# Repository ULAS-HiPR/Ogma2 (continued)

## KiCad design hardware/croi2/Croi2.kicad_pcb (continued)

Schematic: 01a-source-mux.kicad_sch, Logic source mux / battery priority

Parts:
C1101: 10n 16V X7R; C_0603_1608Metric
C1102: 100n 16V X7R; C_0603_1608Metric
C1103: 100n 16V X7R; C_0402_1005Metric; MPN CL05B104KB54PNC; LCSC C307331
C1104, C1105: 1u 16V X7R; C_0603_1608Metric
C1106: 2.2u 16V X7R; C_0603_1608Metric
R1101: 40.2k 0.1%; R_0603_1608Metric
R1102, R1104, R1106: 10k 0.1%; R_0603_1608Metric
R1103: 75k 0.1%; R_0603_1608Metric
R1105: 43.2k 0.1%; R_0603_1608Metric
R1107: 44.2k 1%; R_0603_1608Metric
R1108: 100k; R_0402_1005Metric; MPN 0402WGF1003TCE; LCSC C25741
U1101: TPS2121RUXR; MPN TPS2121RUXR
U1102: TPS70933DBVR; MPN TPS70933DBVR

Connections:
BOOT_3V3: C1106.1, R1108.1, U1102.5 (OUT); also elsewhere on the board
GND: C1101.2, C1102.2, C1103.2, C1104.2, C1105.2, C1106.2, R1102.2, R1104.2, R1106.2, R1107.2, U1101.3 (GND_[3,12]), U1101.12, U1102.2 (GND); also elsewhere on the board
LOGIC_SELECTED: C1104.1, C1105.1, U1101.1 (SUPPLY_[1,8]), U1101.8, U1102.1 (SUPPLY_[1,3]), U1102.3; also elsewhere on the board
MUX_ILIM: R1107.1, U1101.10 (ILIM)
MUX_OV_BAT: R1103.2, R1104.1, U1101.5 (OV1)
MUX_OV_USB: R1105.2, R1106.1, U1101.4 (OV2)
MUX_PR_BAT: R1101.2, R1102.1, U1101.6 (PR1)
MUX_SOURCE_STATUS: R1108.2, U1101.9 (ST)
MUX_SS: C1101.1, U1101.11 (SS)
USB_LIMITED: C1103.1, R1105.1, U1101.2 (IN2); also elsewhere on the board
VBAT_PROTECTED: C1102.1, R1101.1, R1103.1, U1101.7 (IN1); also elsewhere on the board

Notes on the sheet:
Priority threshold ~5.32 V. OV limits ~9.00 V battery and ~5.64 V USB. Normal switchover, not fast XCOMP.
Bootstrap load budget <=1 mA total. The mux limit is ~2.5 A typical; it does not enforce USB compliance.
BATTERY PRIORITY AND OVERVOLTAGE THRESHOLDS
LOGIC SOURCE MUX / BATTERY PRIORITY
BOOTSTRAP BIAS: INDEPENDENT OF FLIGHT / COMMS / OPTIONAL RAILS
What this does: Chooses battery or USB to run the logic. Battery takes priority; this circuit does not charge it. Connects to: Protected battery from 01-power and USB from 04c -> 01c preregulator. 01b decides which downstream circuits may start.

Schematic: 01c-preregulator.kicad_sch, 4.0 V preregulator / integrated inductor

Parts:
C1301: 1u 10V X7R; C_0603_1608Metric
C1302: 100n 16V X7R; C_0402_1005Metric; MPN CL05B104KB54PNC; LCSC C307331
C1303: 100n 25V X7R; C_0603_1608Metric
C1304: 22u 25V X7R; C_1210_3225Metric
C1305, C1306: 47u 16V X6S; C_1210_3225Metric; MPN GRM32EC81C476KE15L
R1301: 30k 0.1%; R_0603_1608Metric
R1302: 10k 0.1%; R_0603_1608Metric
R1303: 16.5k 1%; R_0402_1005Metric; MPN FRC0402F1652TS; LCSC C3013155
R1304: 100k; R_0402_1005Metric; MPN 0402WGF1003TCE; LCSC C25741
TP36: BUCK_PG; TestPoint_Pad_D1.0mm
TP37: LOGIC_SELECTED; TestPoint_Keystone_5190TR_ColorKeyed; MPN 5194TR; LCSC C22388408
TP39: 4V_PRE; TestPoint_Keystone_5190TR_ColorKeyed; MPN 5194TR; LCSC C22388408
U1301: TPSM63603RDHR; MPN TPSM63603RDHR

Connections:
4V_PRE: C1302.1, C1305.1, C1306.1, R1301.1, TP39.1 (1_1), U1301.7, U1301.8, U1301.9, U1301.10, U1301.12, U1301.13, U1301.14, U1301.15, U1301.22 (SUPPLY_[22,7,8,9,10,12,13,14,15,30]), U1301.30; also elsewhere on the board
BOOT_3V3: R1304.1; also elsewhere on the board
BUCK_FB: R1301.2, R1302.1, U1301.25 (FB)
BUCK_PG: R1304.2, TP36.1 (1_1), U1301.26 (PG)
BUCK_RT: R1303.1, U1301.1 (RT)
BUCK_VCC: C1301.1, U1301.23 (VCC)
GND: C1301.2, C1302.2, C1303.2, C1304.2, C1305.2, C1306.2, R1302.2, R1303.2, U1301.5 (GND_[5,6,16,17,24,27,28,29]), U1301.6, U1301.16, U1301.17, U1301.24, U1301.27, U1301.28, U1301.29; also elsewhere on the board
LOGIC_SELECTED: C1303.1, C1304.1, TP37.1 (1_1), U1301.2 (SUPPLY_[2,3,4,18,19]), U1301.3, U1301.4, U1301.18, U1301.19; also elsewhere on the board

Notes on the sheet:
Integrated switching module: no external inductor or bootstrap parts. 800 kHz starting point; nominal 4.0 V output.
What this does: Efficiently reduces the selected input to about 4 V before the quieter 3.3 V regulators. Connects to: 01a source selector -> 01d held flight input, 01comms-limit and 01optional-limit. This is a shared supply, not redundant power.
Feedback senses the real output node. Minimum USB input/dropout, effective output capacitance and conducted/radiated noise still require tests.
4.0 V PREREGULATOR / INTEGRATED INDUCTOR

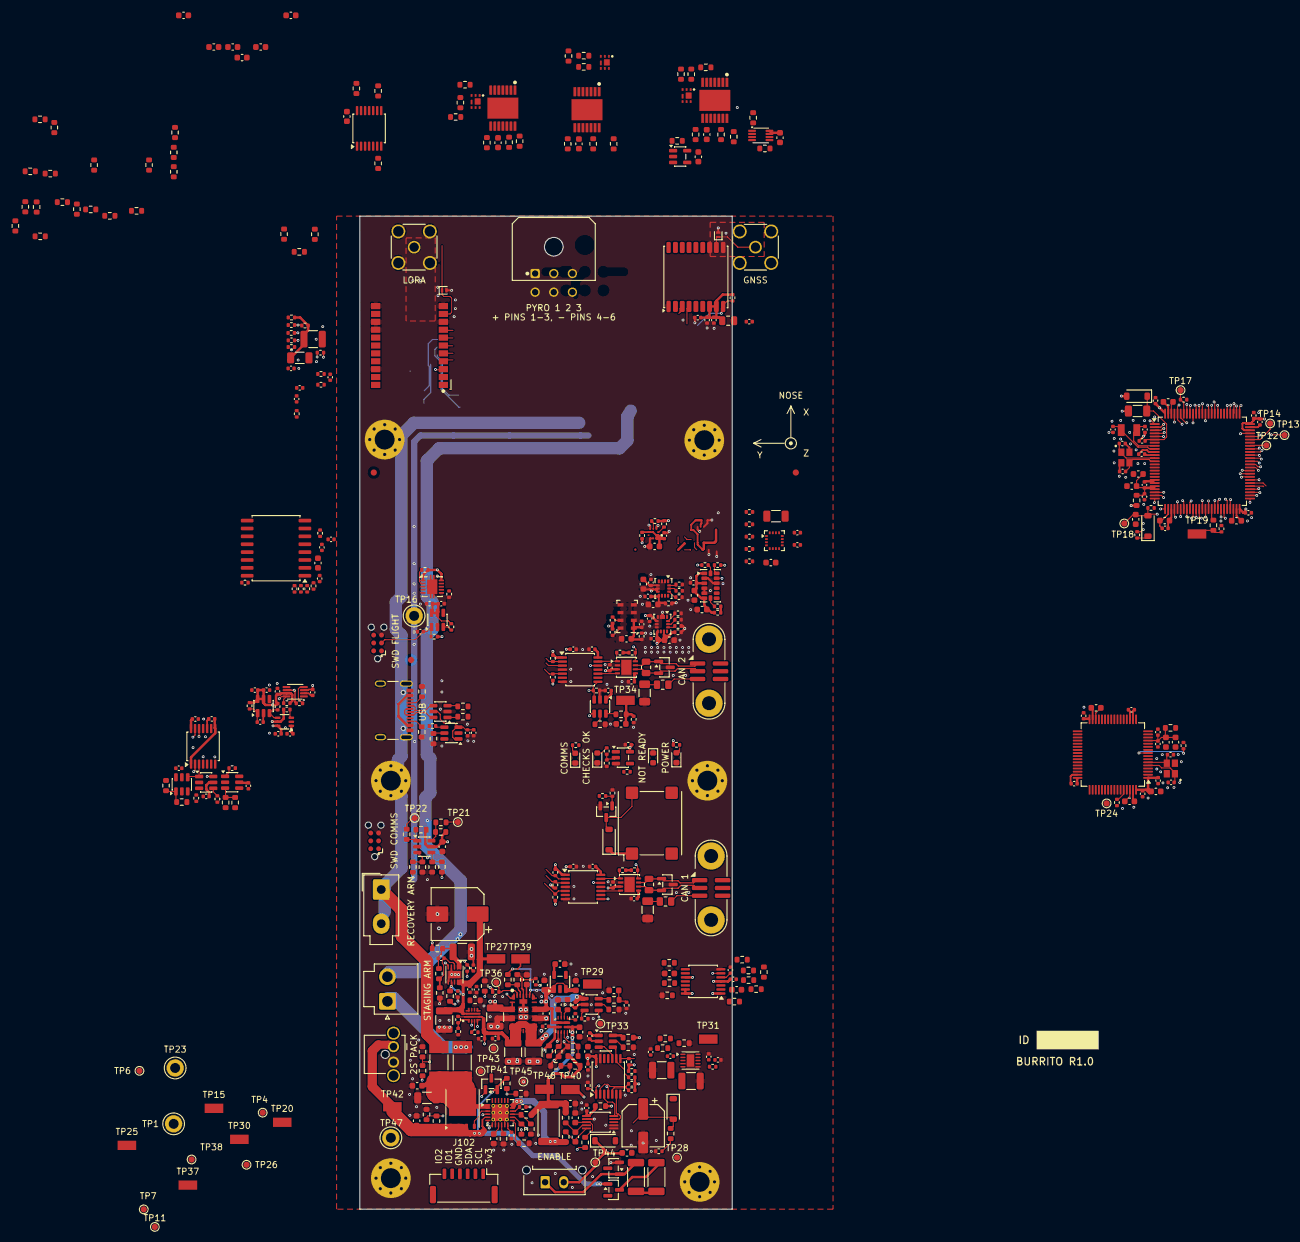
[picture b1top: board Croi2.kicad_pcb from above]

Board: 6 copper layers, 60.0 x 160.0 mm, 509 parts (0 on the bottom side), 281 nets.

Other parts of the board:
C4401, C4402, C4601, C4603, C4604: 100n 16V X7R; C_0402_1005Metric
C6502: 100n 16V X7R; C_0603_1608Metric
C6504: 100n 25V X7R; C_0603_1608Metric
D4401: USBLC6-2SC6; SOT-23-6
FID1, FID2, FID3: Fiducial; Fiducial_1mm_Mask2mm
H3, H4, H5, H6, H7, H8: M3; MountingHole_3.2mm_M3_Pad_Via
J4401: USB4105-GF-A
MK1: MARK_AXES
Q6501: CSD17318Q2
R4401, R4402: 5.1k 1%; R_0603_1608Metric
R4403: 60.4k 1%; R_0603_1608Metric
R4405, R4406: 22R; R_0603_1608Metric
R4407: 100k; R_0402_1005Metric
R4604, R4605: 47k; R_0402_1005Metric
R6501, R6502, R6503, R6505: 100k; R_0603_1608Metric
R6504: 100R; R_0603_1608Metric
R6510: 0R ENERGY LINK - DNP; R_0603_1608Metric
R6514: 1.24k 1%; R_0603_1608Metric
U4401: TPS2553DBVR-1
U6502: SN74LVC1G08DBVR; SOT-23-5
U6504: TPS1H100BQPWPRQ1

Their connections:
BOOT_3V3: R4407.1; also elsewhere on the board
COMMS_3V3: C4601.1, C4603.1, C4604.1, R4604.1, R4605.1; also elsewhere on the board
FLIGHT_3V3: C6502.1, U6502.5 (VCC), U6504.12 (DIAG_EN); also elsewhere on the board
GND: C4401.2, C4402.2, C4601.2, C4603.2, C4604.2, C6502.2, C6504.2, D4401.2 (GND), H3.1, H4.1, H5.1, H6.1, H7.1, H8.1, J4401.A1 (GND), J4401.A12 (GND), J4401.B1 (GND), J4401.B12 (GND), J4401.S1 (SHIELD), Q6501.4 (GND_[4,7]), Q6501.7, R4401.2, R4402.2, R4403.2, R6501.2, R6502.2, R6503.2, R6505.2, R6514.2, U4401.2 (GND), U6502.3 (GND), U6504.2 (GND_[2,15]), U6504.15; also elsewhere on the board
LORA_NCS: R4604.2; also elsewhere on the board
LORA_RESET_N: R4605.2; also elsewhere on the board
OUTPUT3_HIGH: U6504.5 (OUT_[5,6,7]), U6504.6, U6504.7; also elsewhere on the board
OUTPUT3_LOW: Q6501.1 (D/D_EP_[1,2,5,6,8]), Q6501.2, Q6501.5, Q6501.6, Q6501.8; also elsewhere on the board
PYRO3_CL: R6514.1, U6504.13 (CL)
PYRO3_ENERGY: C6504.1, R6510.2, U6504.8 (VS_[8,9,10]), U6504.9, U6504.10
PYRO3_FIRE: R6501.1, U6502.1; also elsewhere on the board
PYRO3_GATE: Q6501.3 (G), R6504.2, R6505.1
PYRO3_HS_ENABLE: R6503.1, U6502.4, U6504.3 (IN)
PYRO3_LS_SELECT: R6502.1, R6504.1; also elsewhere on the board
STAGE_ELIGIBLE: U6502.2; also elsewhere on the board
STAGING_ARMED_VBAT: R6510.1; also elsewhere on the board
USB_CC1: J4401.A5 (CC1), R4401.1
USB_CC2: J4401.B5 (CC2), R4402.1
USB_CONN_D+: D4401.1 (I/O1), D4401.6 (I/O1), J4401.A6 (D+), J4401.B6 (D+), R4405.2
USB_CONN_D-: D4401.3 (I/O2), D4401.4 (I/O2), J4401.A7 (D-), J4401.B7 (D-), R4406.2
USB_D+: R4405.1; also elsewhere on the board
USB_D-: R4406.1; also elsewhere on the board
USB_ILIM: R4403.1, U4401.5 (ILIM)
USB_LIMITED: U4401.6 (OUT); also elsewhere on the board
USB_LIMIT_FAULT_N: R4407.2, U4401.4 (~FAULT)
USB_VBUS: C4401.1, C4402.1, D4401.5 (VBUS), J4401.A4 (VBUS), J4401.A9 (VBUS), J4401.B4 (VBUS), J4401.B9 (VBUS), U4401.1 (IN), U4401.3 (EN); also elsewhere on the board

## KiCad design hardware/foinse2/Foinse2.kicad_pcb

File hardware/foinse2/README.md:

# Foinse2

8 September 2026. Readable, connected engineering draft. Not ready for manufacture or flight.

Open [Foinse2.kicad_pro](Foinse2.kicad_pro), then its schematic and PCB from that project.
Reopen old editors without saving stale in-memory drawings over these files.

12 schematic pages, 113 physical symbols, 112 assigned PCB footprints.
Each circuit explains what it does and what it connects to. Follow the root
index, then trace the local wires. Labels identify connections between sheets.

The external master-enable contacts are implemented in the draft.
Read the [installation change record](installation-change-record.md) for exact
parts, connector pins, limitations and required tests.

Existing component positions, angles, sides and PCB identities are preserved.
12 new footprints are staged outside the provisional outline for Seán to
integrate. No automatic routing or further packing was done. Native identities
and pad nets match the schematic; GUI cross-selection itself was not exercised.
Both editors must use this project for native cross-probing.

- [Current engineering status](schematic-status.md).
- [Schematic checks](full-checks.json), [PCB checks](board-checks.json),
  [independent identity checks](native-identity-checks.json).
- [Local library inventory](libraries/board-library-manifest.json).
- [Architecture reading pack](../../docs/architecture/README.md).
- [Earlier README, preserved as history](history/pre-readable-2026-09-08/README.md).

Current ERC: zero findings. PCB DRC: 24 findings, plus unrouted
connections and missing J101 Nano-Fit. These are not clean release files.
Exact models remain incomplete. Pack-specific fusing, charging service and actuator requirements remain open.
There is no MCU, onboard charger or regulated 24 V stage.

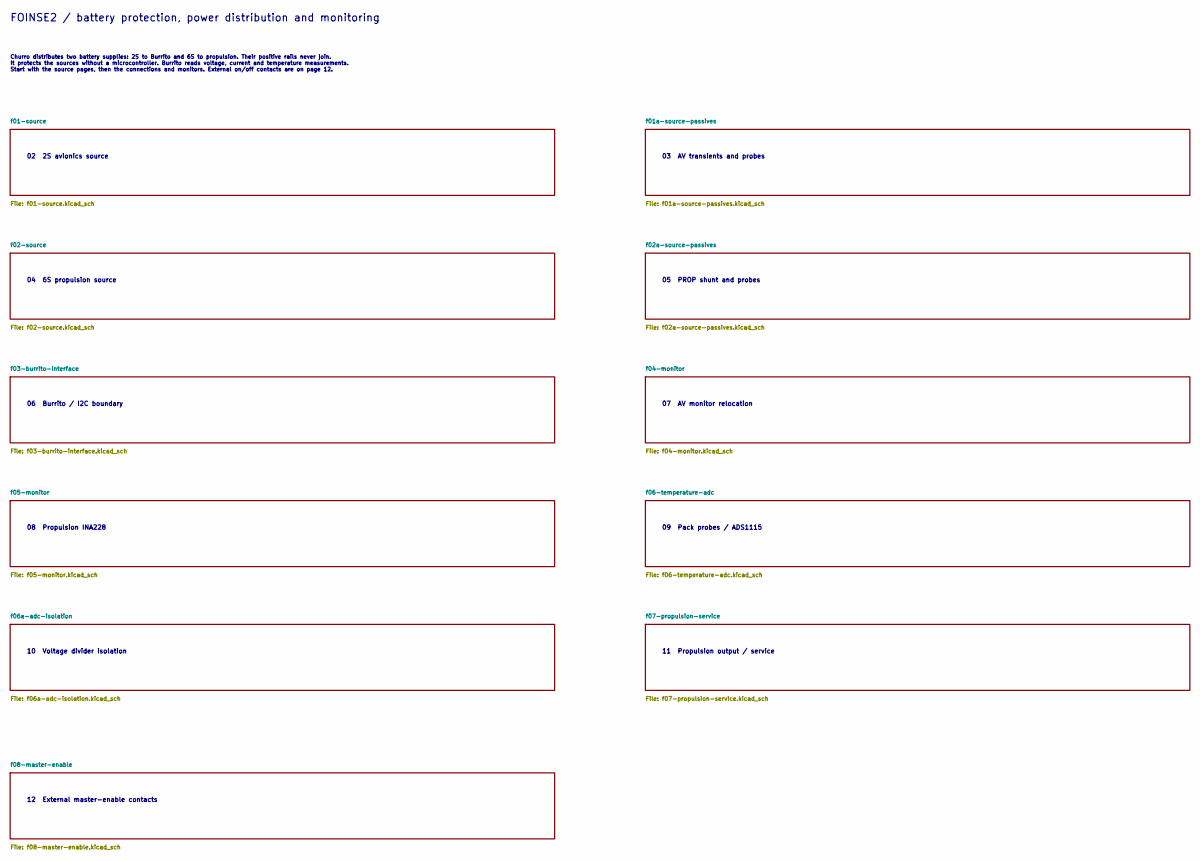
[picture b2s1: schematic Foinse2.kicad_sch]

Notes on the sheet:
02 2S avionics source
03 AV transients and probes
04 6S propulsion source
05 PROP shunt and probes
06 Burrito / I2C boundary
07 AV monitor relocation
08 Propulsion INA228
09 Pack probes / ADS1115
10 Voltage divider isolation
11 Propulsion output / service
FOINSE2 / battery protection, power distribution and monitoring
Churro distributes two battery supplies: 2S to Burrito and 6S to propulsion. Their positive rails never join. It protects the sources without a microcontroller. Burrito reads voltage, current and temperature measurements. Start with the source pages, then the connections and monitors. External on/o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
12 External master-enable contacts

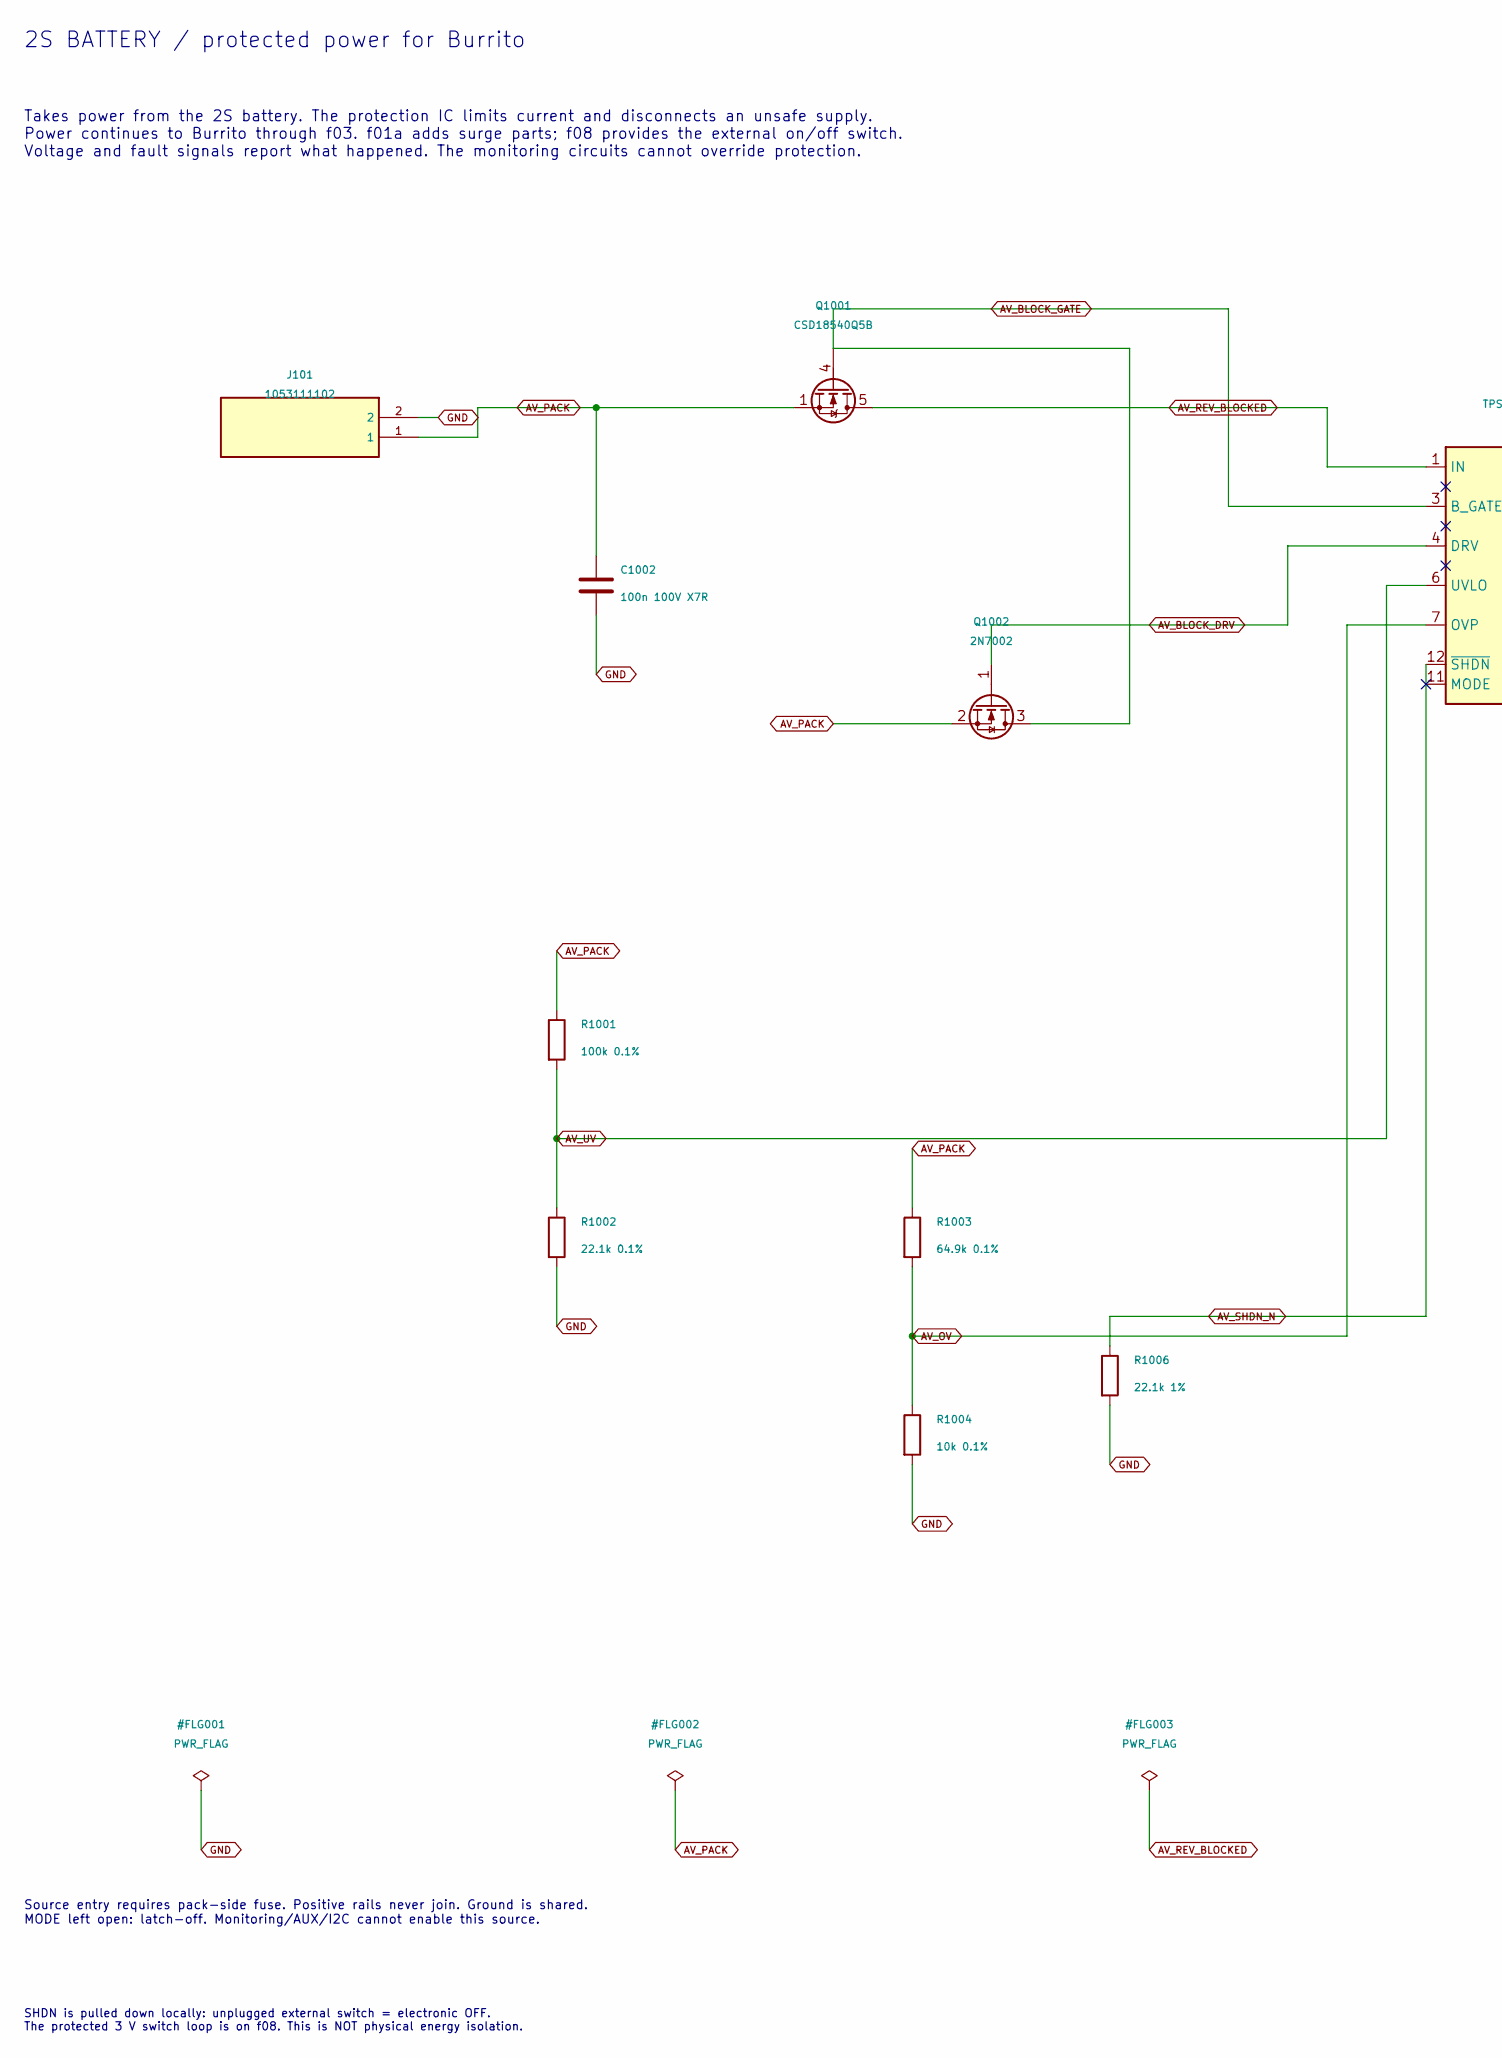
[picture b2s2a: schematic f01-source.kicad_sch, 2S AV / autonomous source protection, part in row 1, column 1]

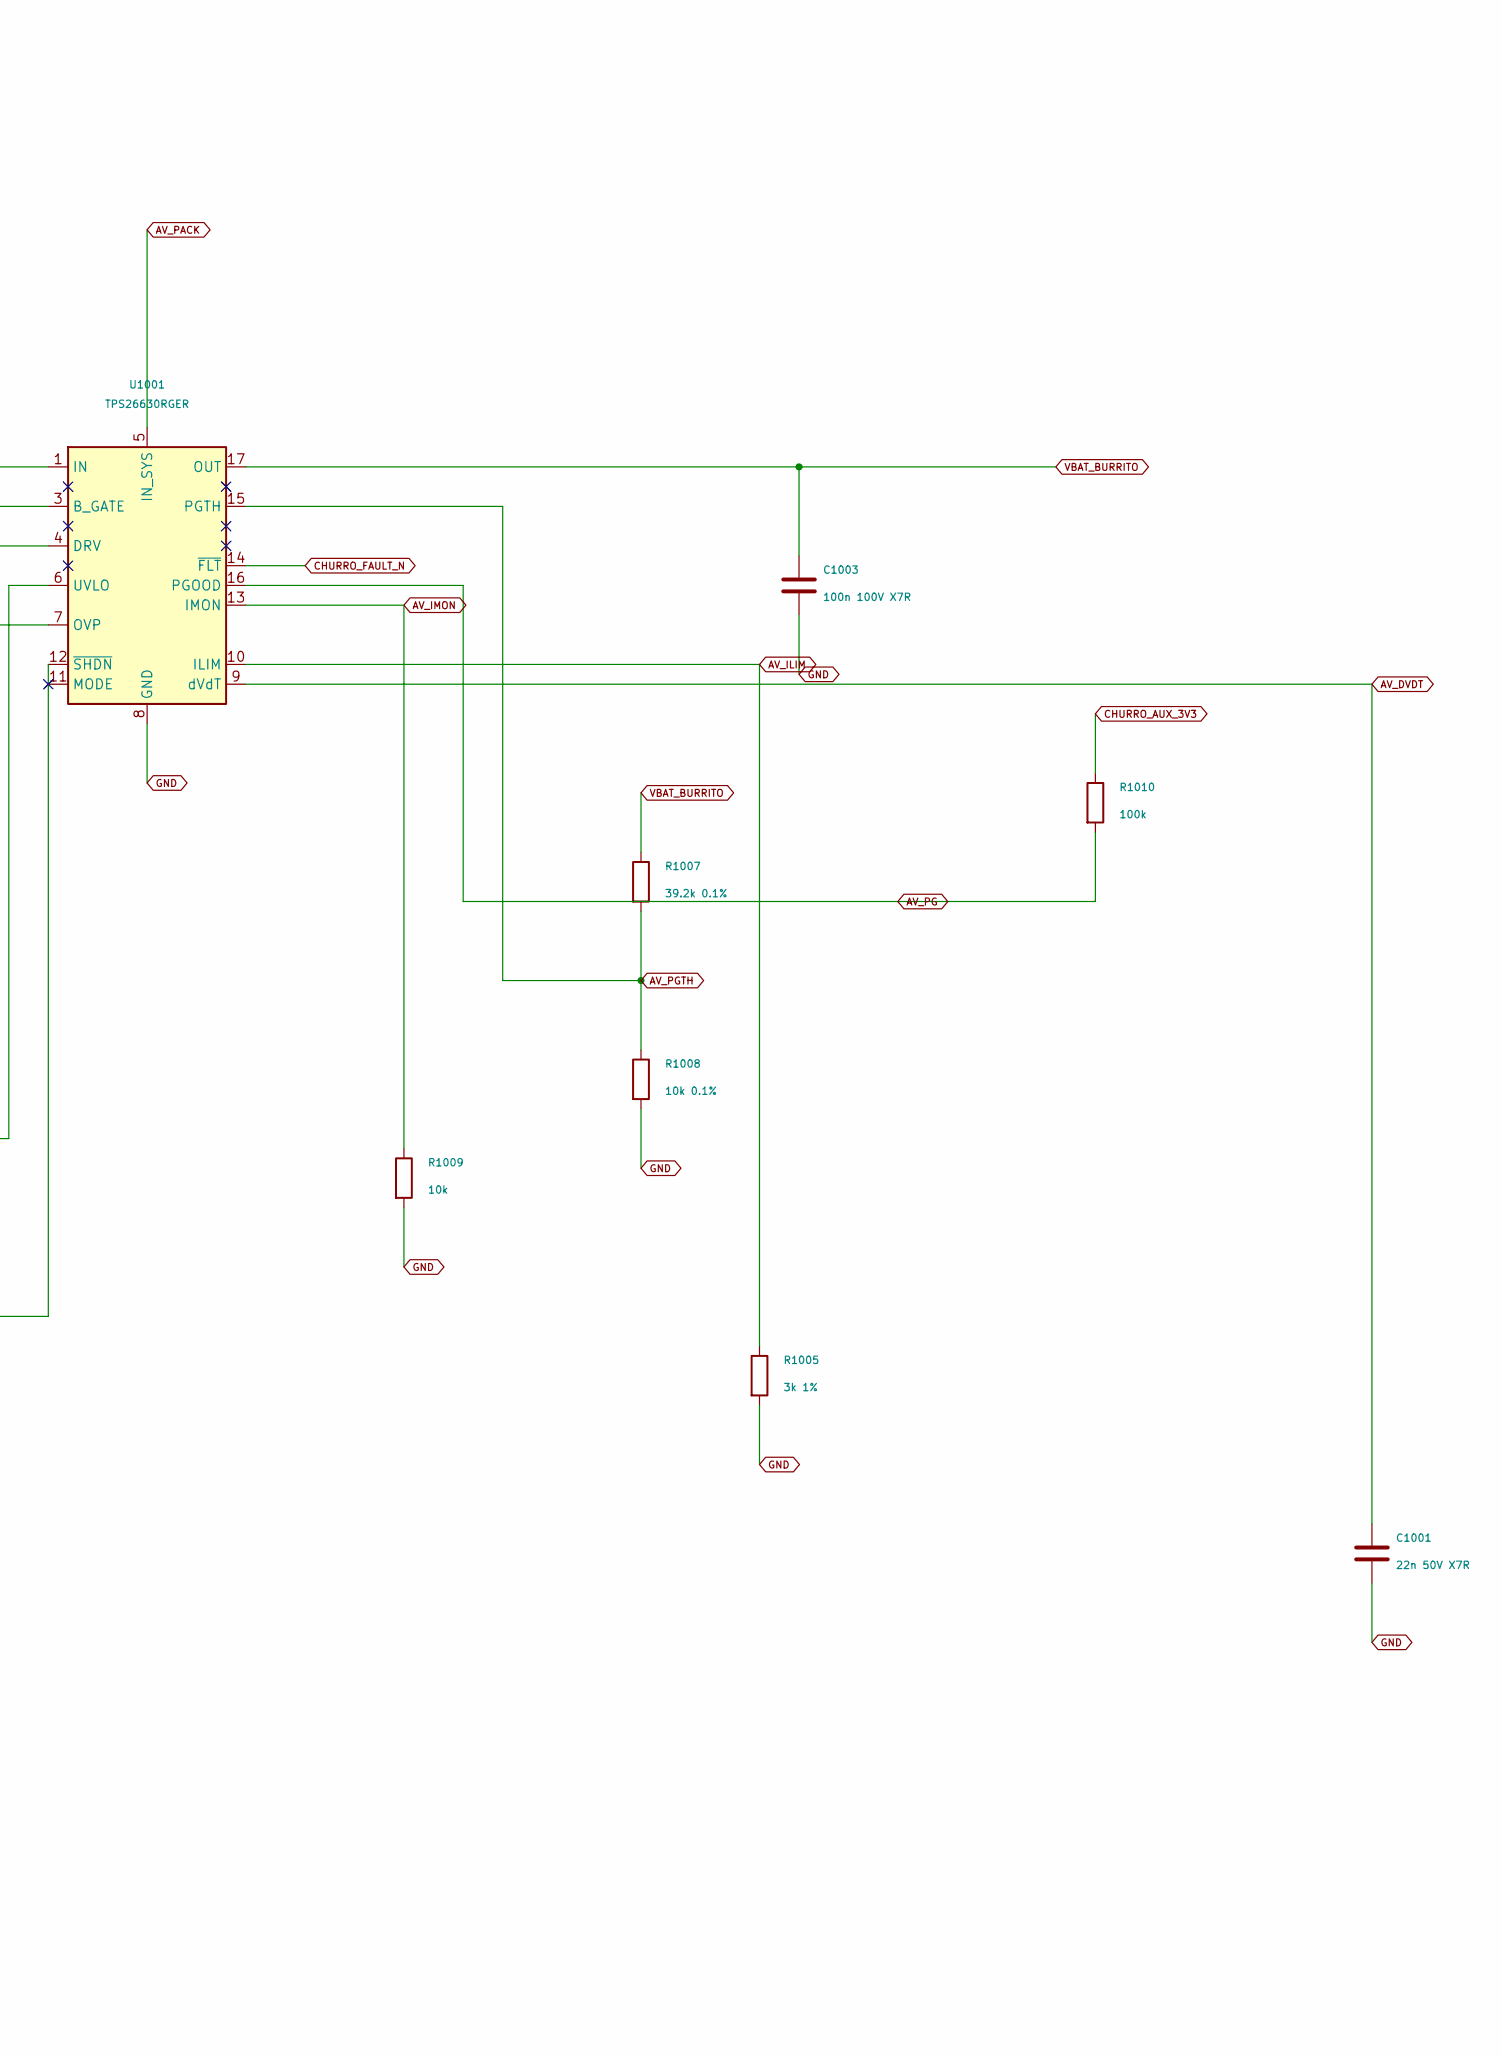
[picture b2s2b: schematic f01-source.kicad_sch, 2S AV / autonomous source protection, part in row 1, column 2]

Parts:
C1001: 22n 50V X7R; C_0603_1608Metric
C1002, C1003: 100n 100V X7R; C_0603_1608Metric
J101: 1053111102; MPN 1053111102
Q1001: CSD18540Q5B; MPN CSD18540Q5B
Q1002: 2N7002; SOT-23
R1001: 100k 0.1%; R_0603_1608Metric
R1002: 22.1k 0.1%; R_0603_1608Metric
R1003: 64.9k 0.1%; R_0603_1608Metric
R1004, R1008: 10k 0.1%; R_0603_1608Metric
R1005: 3k 1%; R_0603_1608Metric
R1006: 22.1k 1%; R_0603_1608Metric
R1007: 39.2k 0.1%; R_0603_1608Metric
R1009: 10k; R_0603_1608Metric
R1010: 100k; R_0603_1608Metric
U1001: TPS26630RGER; MPN TPS26630RGER

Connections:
AV_BLOCK_DRV: Q1002.1 (G), U1001.4 (DRV)
AV_BLOCK_GATE: Q1001.4 (G), Q1002.3 (D), U1001.3 (B_GATE); also elsewhere on the board
AV_DVDT: C1001.1, U1001.9 (dVdT)
AV_ILIM: R1005.1, U1001.10 (ILIM)
AV_IMON: R1009.1, U1001.13 (IMON); also elsewhere on the board
AV_OV: R1003.2, R1004.1, U1001.7 (OVP)
AV_PACK: C1002.1, J101.1, Q1001.1 (S), Q1001.2 (S), Q1001.3 (S), Q1002.2 (S), R1001.1, R1003.1, U1001.5 (IN_SYS); also elsewhere on the board
AV_PG: R1010.2, U1001.16 (PGOOD); also elsewhere on the board
AV_PGTH: R1007.2, R1008.1, U1001.15 (PGTH)
AV_REV_BLOCKED: Q1001.5 (D), U1001.1 (IN), U1001.2 (IN); also elsewhere on the board
AV_SHDN_N: R1006.1, U1001.12 (~SHDN); also elsewhere on the board
AV_UV: R1001.2, R1002.1, U1001.6 (UVLO)
CHURRO_AUX_3V3: R1010.1; also elsewhere on the board
CHURRO_FAULT_N: U1001.14 (~FLT); also elsewhere on the board
GND: C1001.2, C1002.2, C1003.2, J101.2, R1002.2, R1004.2, R1005.2, R1006.2, R1008.2, R1009.2, U1001.8 (GND), U1001.25 (GND); also elsewhere on the board
VBAT_BURRITO: C1003.1, R1007.1, U1001.17 (OUT), U1001.18 (OUT); also elsewhere on the board

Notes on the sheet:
2S BATTERY / protected power for Burrito
Source entry requires pack-side fuse. Positive rails never join. Ground is shared. MODE left open: latch-off. Monitoring/AUX/I2C cannot enable this source.
SHDN is pulled down locally: unplugged external switch = electronic OFF. The protected 3 V switch loop is on f08. This is NOT physical energy isolation.
Takes power from the 2S battery. The protection IC limits current and disconnects an unsafe supply. Power continues to Burrito through f03. f01a adds surge parts; f08 provides the external on/off switch. Voltage and fault signals report what happened. The monitoring circuits cannot override protect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

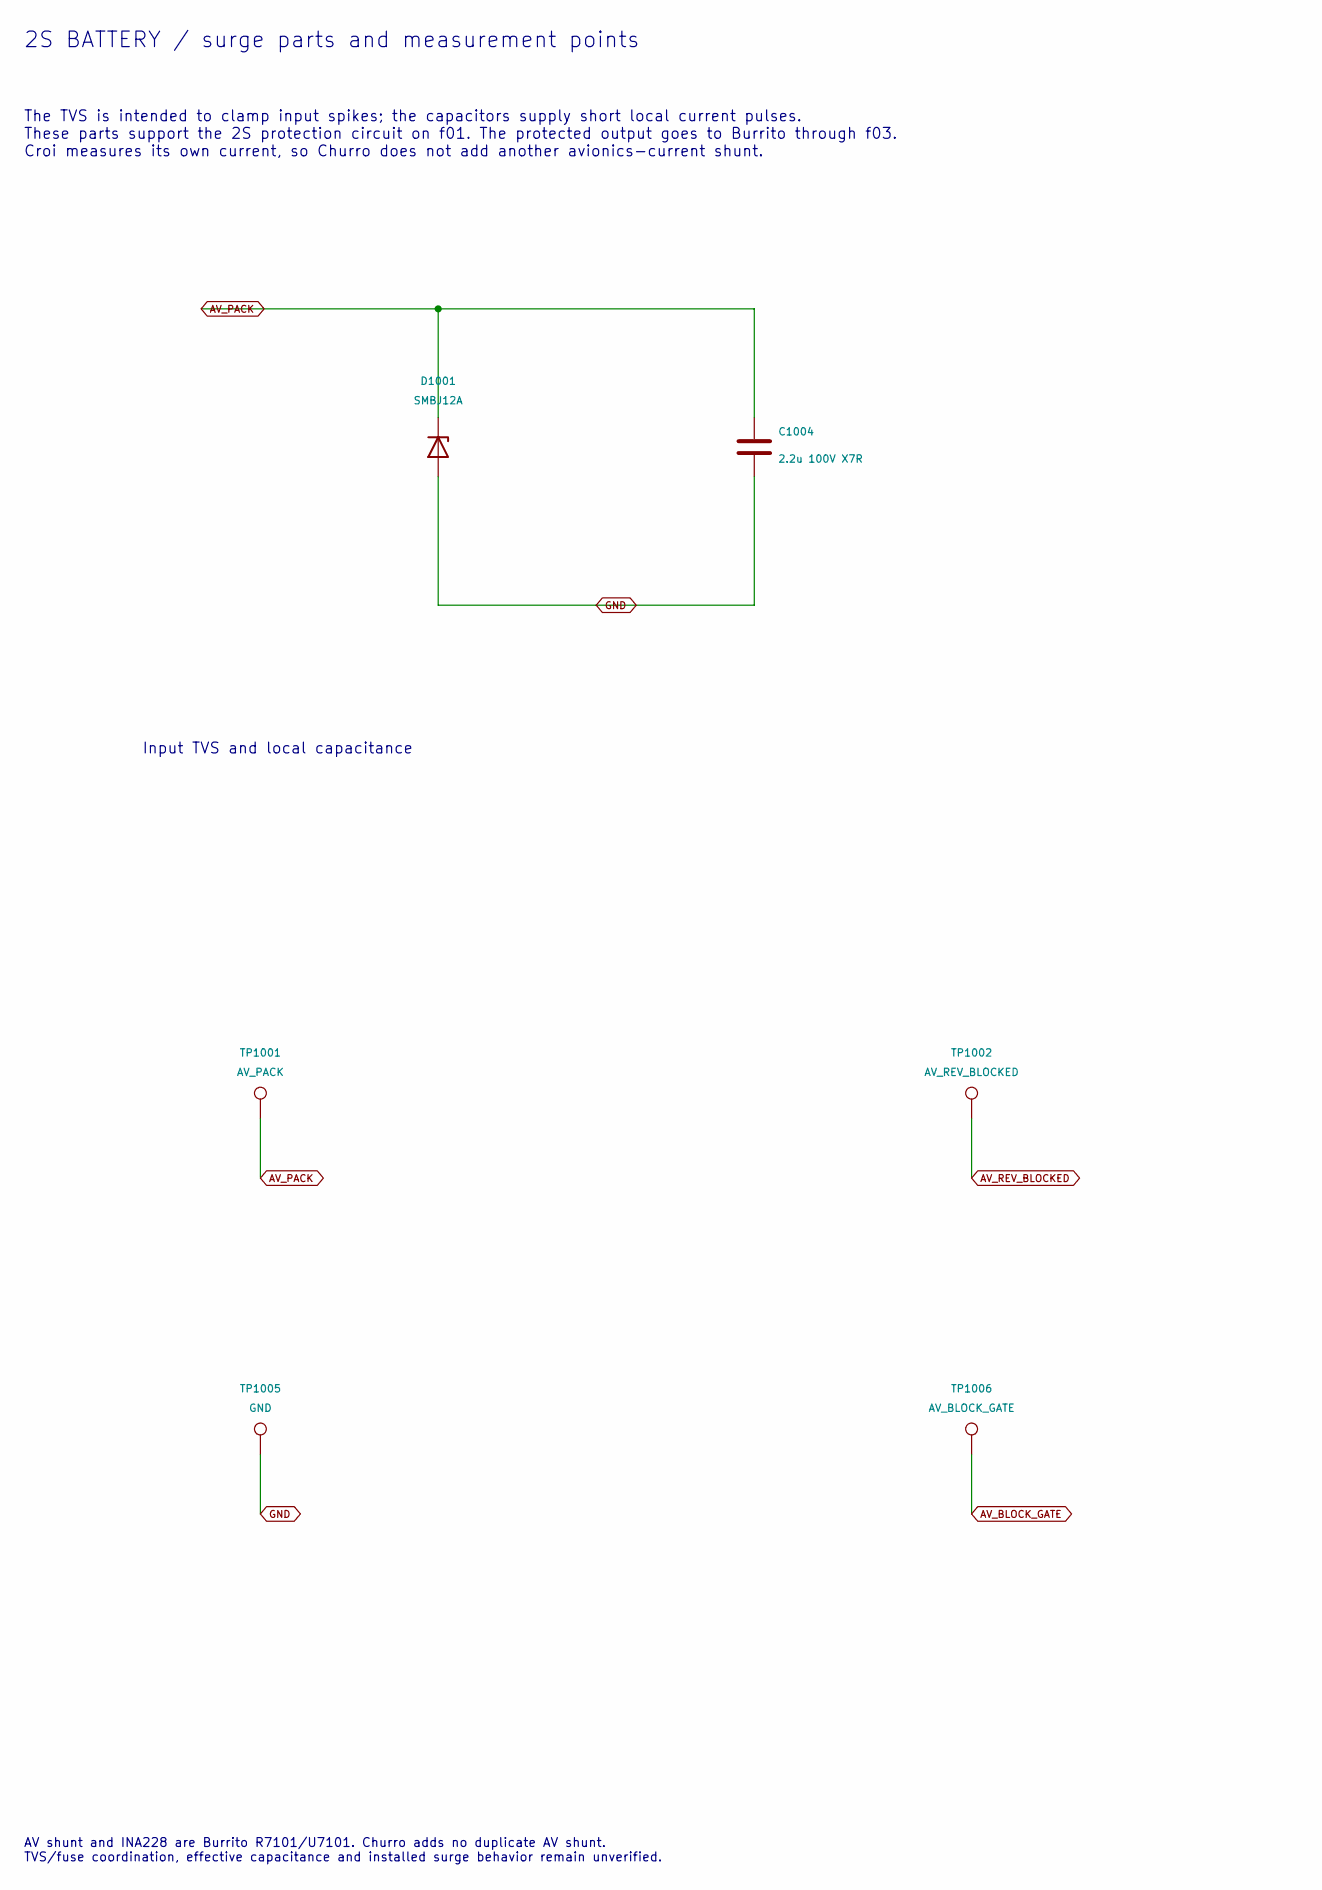
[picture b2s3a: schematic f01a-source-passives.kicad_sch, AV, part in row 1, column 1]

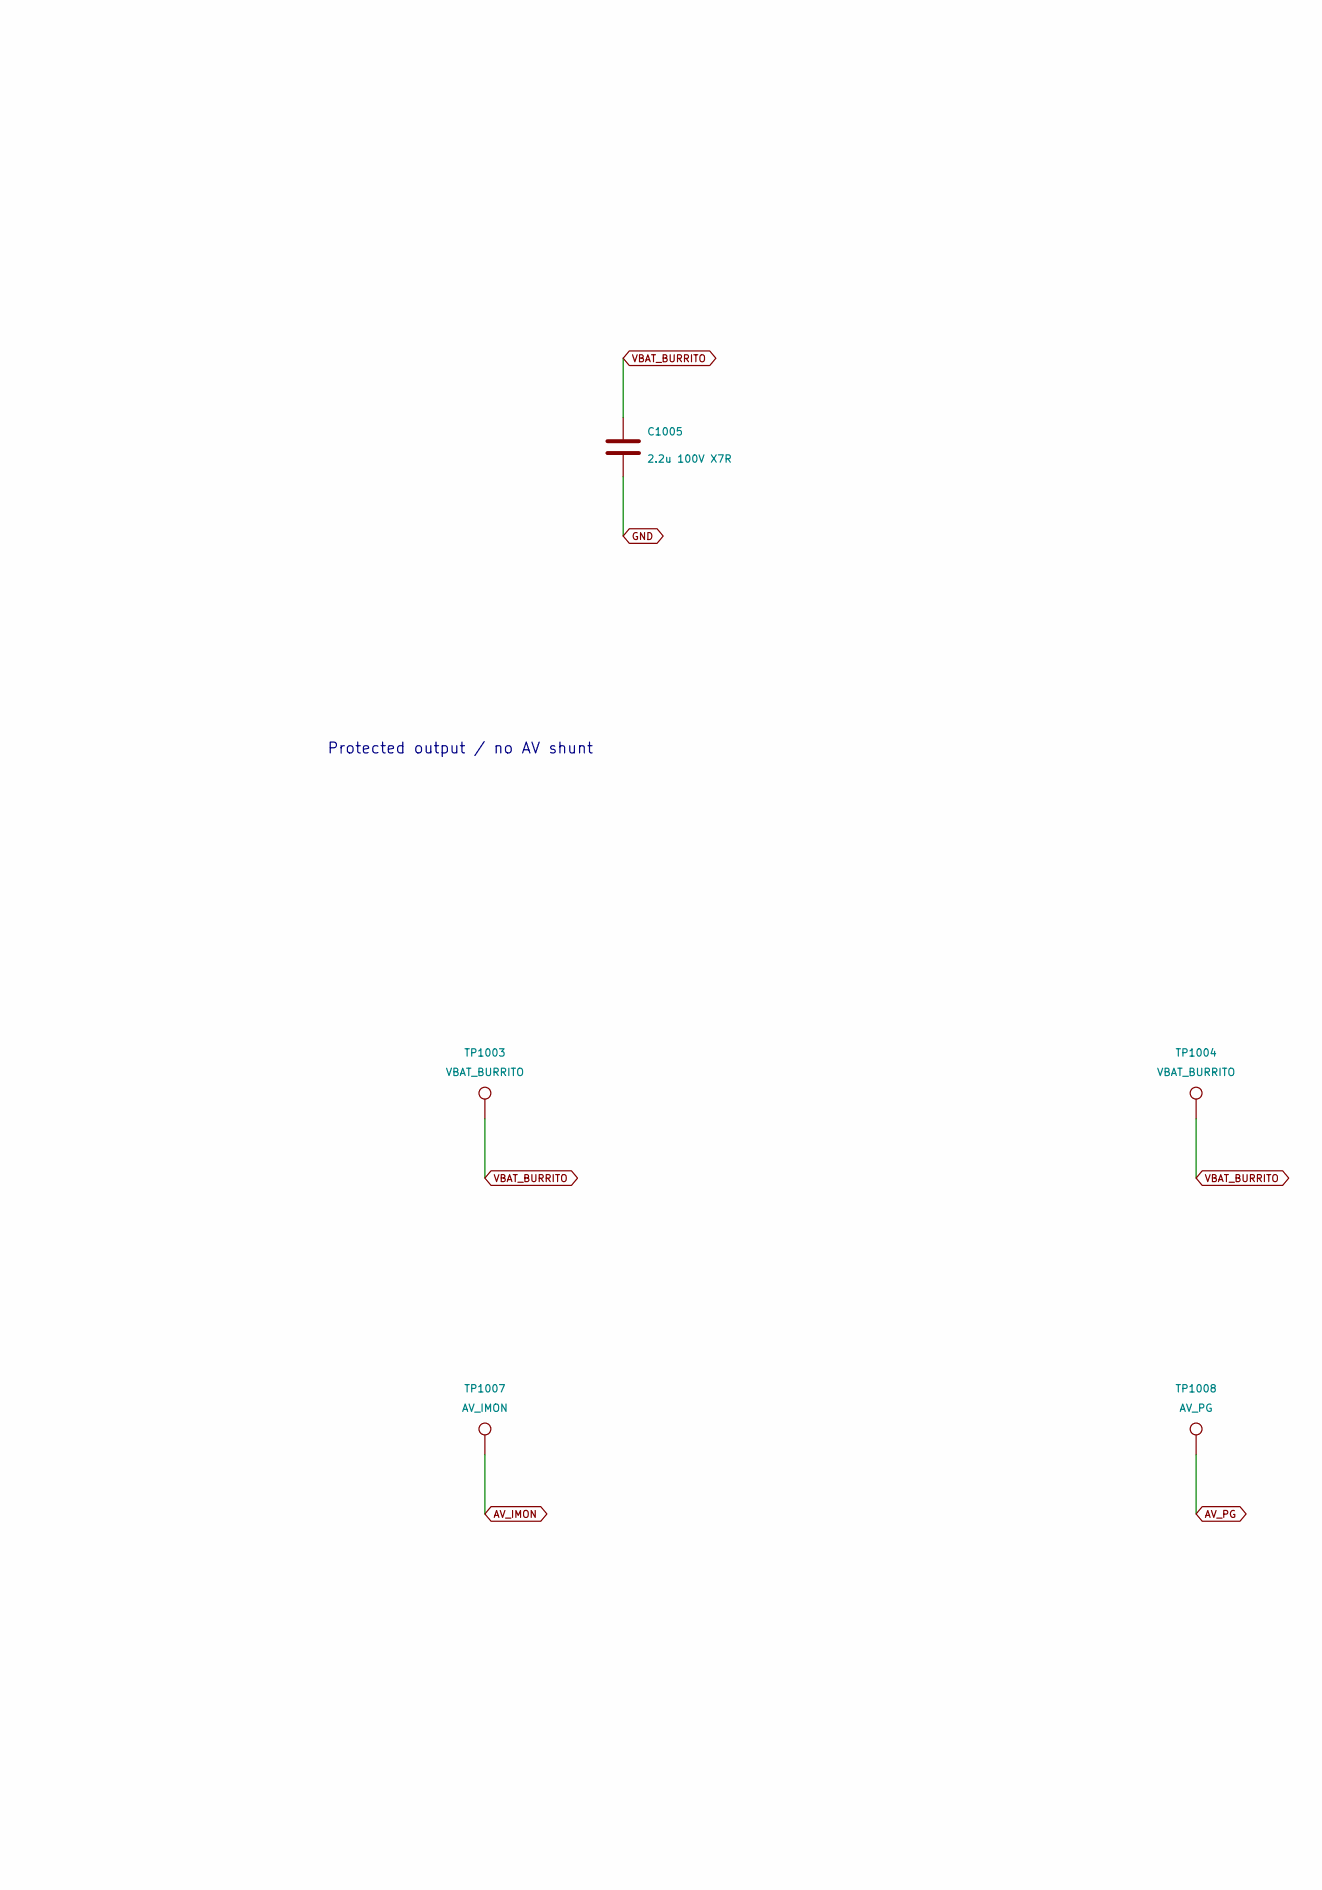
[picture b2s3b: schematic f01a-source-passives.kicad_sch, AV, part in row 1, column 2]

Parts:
C1004, C1005: 2.2u 100V X7R; C_1210_3225Metric
D1001: SMBJ12A; D_SMB
TP1001: AV_PACK; TestPoint_Loop_D2.50mm_Drill1.0mm
TP1002: AV_REV_BLOCKED; TestPoint_Loop_D2.50mm_Drill1.0mm
TP1003, TP1004: VBAT_BURRITO; TestPoint_Loop_D2.50mm_Drill1.0mm
TP1005: GND; TestPoint_Loop_D2.50mm_Drill1.0mm
TP1006: AV_BLOCK_GATE; TestPoint_Pad_D1.0mm
TP1007: AV_IMON; TestPoint_Pad_D1.0mm
TP1008: AV_PG; TestPoint_Pad_D1.0mm

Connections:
AV_BLOCK_GATE: TP1006.1; also elsewhere on the board
AV_IMON: TP1007.1; also elsewhere on the board
AV_PACK: C1004.1, D1001.1 (K), TP1001.1; also elsewhere on the board
AV_PG: TP1008.1; also elsewhere on the board
AV_REV_BLOCKED: TP1002.1; also elsewhere on the board
GND: C1004.2, C1005.2, D1001.2 (A), TP1005.1; also elsewhere on the board
VBAT_BURRITO: C1005.1, TP1003.1, TP1004.1; also elsewhere on the board

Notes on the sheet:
2S BATTERY / surge parts and measurement points
Input TVS and local capacitance
Protected output / no AV shunt
AV shunt and INA228 are Burrito R7101/U7101. Churro adds no duplicate AV shunt. TVS/fuse coordination, effective capacitance and installed surge behavior remain unverified.
The TVS is intended to clamp input spikes; the capacitors supply short local current pulses. These parts support the 2S protection circuit on f01. The protected output goes to Burrito through f03. Croi measures its own current, so Churro does not add another avionics-current shunt.
